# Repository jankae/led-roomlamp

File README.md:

# led-roomlamp
The led-roomlamp consists of up to six LED spots connected to a central baseplate.

Each spot features a 10W LED on a heatsink with its own (AVR controller) boost-converter (led-driver):

The spot needs a 12V supply and can be controlled via I2C. All the spots are connected to the central led-control board on the baseplate:

The led-control board essentially is just an ATmega328 with a switching controller, a microphone (one of the available MAX9814 breakout-boards) and (optionally) an ESP-01.

The controller continuously samples the microphone, performs an FFT and identifies whistle tones. By whistling different frequencies, the brightness of the lamp can be controlled.

Alternatively, the lamp can be controlled via UART (38400 Baud) which is connected to the ESP. Using the [ESP-link](https://github.com/jeelabs/esp-link) firmware, commands can be send via WiFi. Send 'help' to retrieve a list of available commands.

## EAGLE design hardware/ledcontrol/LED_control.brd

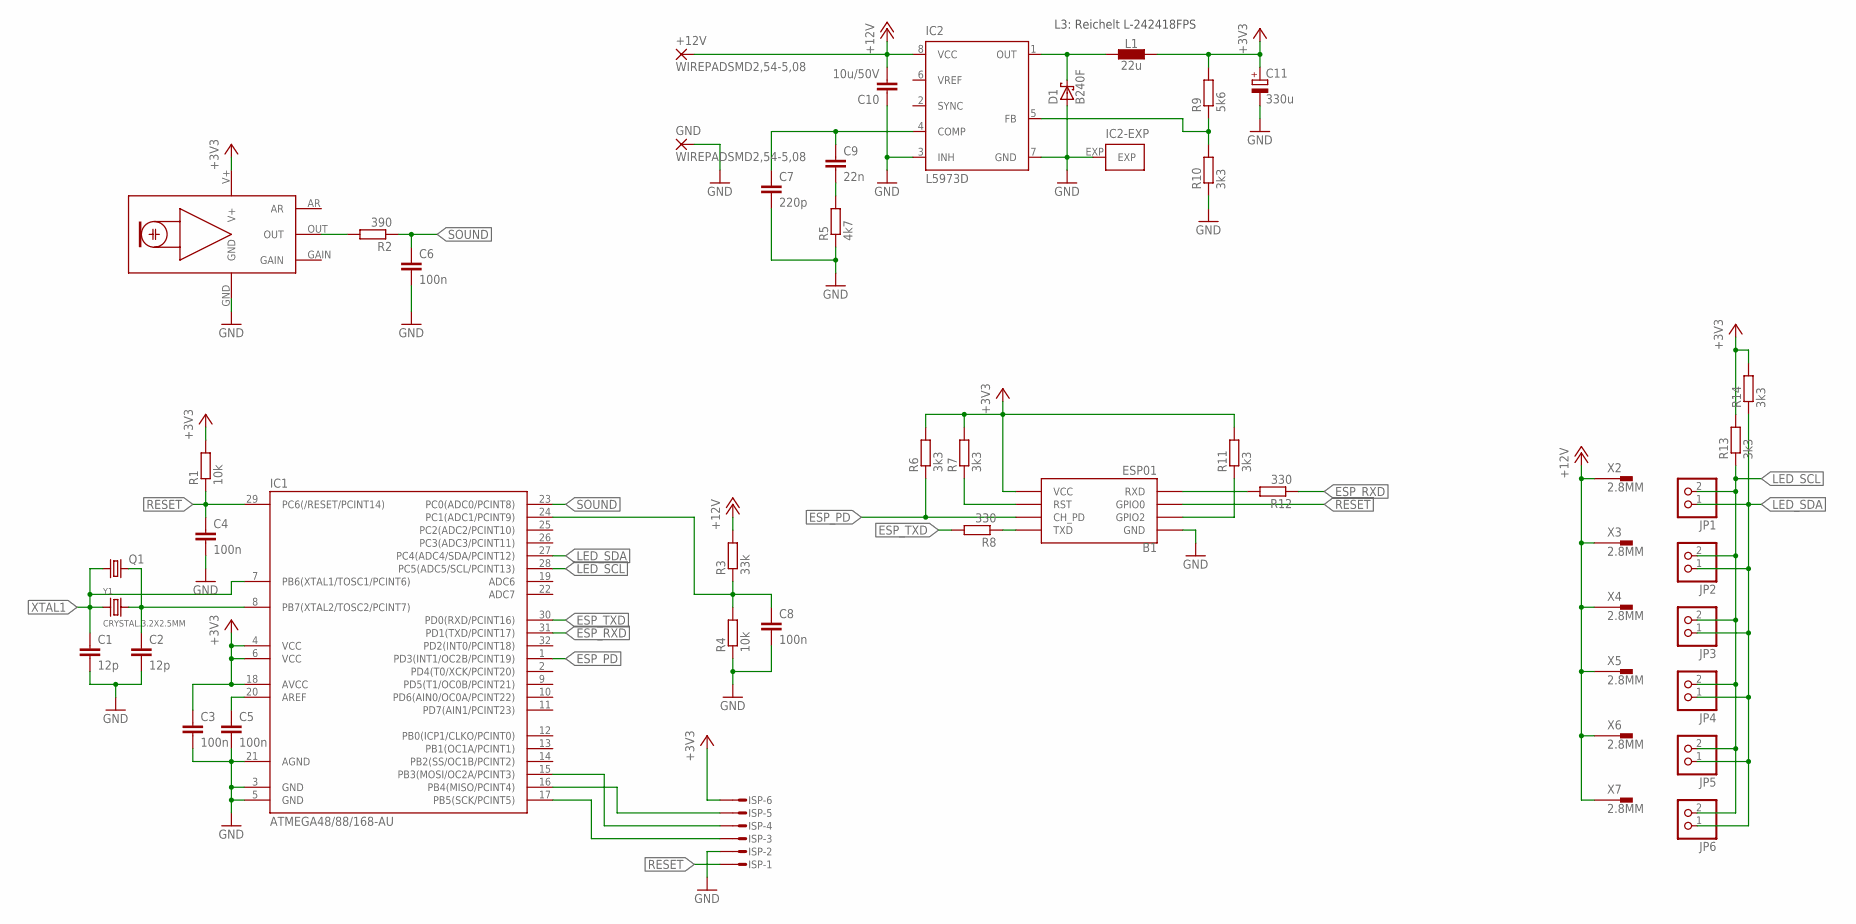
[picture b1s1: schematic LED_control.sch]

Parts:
+12V: WIREPADSMD2,54-5,08; SMD2,54-5,08
B1: ESP01
C1, C2: 12p; C0603K
C3, C5, C6: 100n; C0603K
C4, C8: 100n; C0603
C7: 220p; C0603
C9: 22n; C0603
C10: 10u/50V; C1206
C11: 330u; 153CLV-0605
D1: B240F; SMB
GND: WIREPADSMD2,54-5,08; SMD2,54-5,08
IC1: ATMEGA48/88/168-AU; TQFP32-08
IC2: L5973D; HSOP8
ISP: MICROMATCH-6SMF; MMT-F-SMD-6
JP1, JP2, JP3, JP4, JP5, JP6: PINHD-1X2/90; 1X02/90
L1: 22u; L_NR60XX
PCB1: MAX9814_AGC_MIC
Q1: CRYSTALHC49S; HC49/S
R1, R4: 10k; R0603
R2: 390; R0603
R3: 33k; R0603
R5: 4k7; R0603
R6, R7, R10, R11, R13, R14: 3k3; R0603
R8, R12: 330; R0603
R9: 5k6; R0603
X2, X3, X4, X5, X6, X7: 2.8MM; 2.8_90
Y1: CRYSTAL.3.2X2.5MM; 3.2X2.5MM

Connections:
+3V3: B1.VCC, C3.1, C11.+, IC1.4 (VCC), IC1.6 (VCC), IC1.18 (AVCC), ISP.6, L1.2, PCB1.V+, R1.2, R6.2, R7.2, R9.2, R11.2, R13.2, R14.2
+12V: +12V.1, C10.2, IC2.8 (VCC), R3.2, X2.1A, X2.1B, X3.1A, X3.1B, X4.1A, X4.1B, X5.1A, X5.1B, X6.1A, X6.1B, X7.1A, X7.1B
ESP_GPIO2: B1.GPIO2, R11.1
ESP_PD: B1.CH_PD, IC1.1 (PD3(INT1/OC2B/PCINT19)), R6.1
ESP_RST: B1.RST, R7.1
ESP_RXD: IC1.31 (PD1(TXD/PCINT17)), R12.1
ESP_TXD: IC1.30 (PD0(RXD/PCINT16)), R8.2
GND: B1.GND, C1.2, C2.2, C3.2, C4.2, C5.2, C6.2, C7.2, C8.2, C10.1, C11.-, D1.A, GND.1, IC1.3 (GND), IC1.5 (GND), IC1.21 (AGND), IC2.3 (INH), IC2.7 (GND), IC2.EXP, ISP.2, PCB1.GND, R4.1, R5.1, R10.1
LED_SCL: IC1.28 (PC5(ADC5/SCL/PCINT13)), JP1.2, JP2.2, JP3.2, JP4.2, JP5.2, JP6.2, R13.1
LED_SDA: IC1.27 (PC4(ADC4/SDA/PCINT12)), JP1.1, JP2.1, JP3.1, JP4.1, JP5.1, JP6.1, R14.1
MISO: IC1.16 (PB4(MISO/PCINT4)), ISP.5
MOSI: IC1.15 (PB3(MOSI/OC2A/PCINT3)), ISP.4
unnamed: B1.RX (RXD), R12.2
unnamed: B1.TX (TXD), R8.1
unnamed: C5.1, IC1.20 (AREF)
unnamed: PCB1.OUT, R2.2
unnamed: C8.1, IC1.24 (PC1(ADC1/PCINT9)), R3.1, R4.2
unnamed: C7.1, C9.1, IC2.4 (COMP)
unnamed: C9.2, R5.2
unnamed: D1.C, IC2.1 (OUT), L1.1
unnamed: IC2.5 (FB), R9.1, R10.2
RESET: B1.GPIO0, C4.1, IC1.29 (PC6(/RESET/PCINT14)), ISP.1, R1.1
SCK: IC1.17 (PB5(SCK/PCINT5)), ISP.3
SOUND: C6.1, IC1.23 (PC0(ADC0/PCINT8)), R2.1
XTAL1: C1.1, IC1.7 (PB6(XTAL1/TOSC1/PCINT6)), Q1.1, Y1.1
XTAL2: C2.1, IC1.8 (PB7(XTAL2/TOSC2/PCINT7)), Q1.2, Y1.3 (2)

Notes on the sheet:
L3: Reichelt L-242418FPS

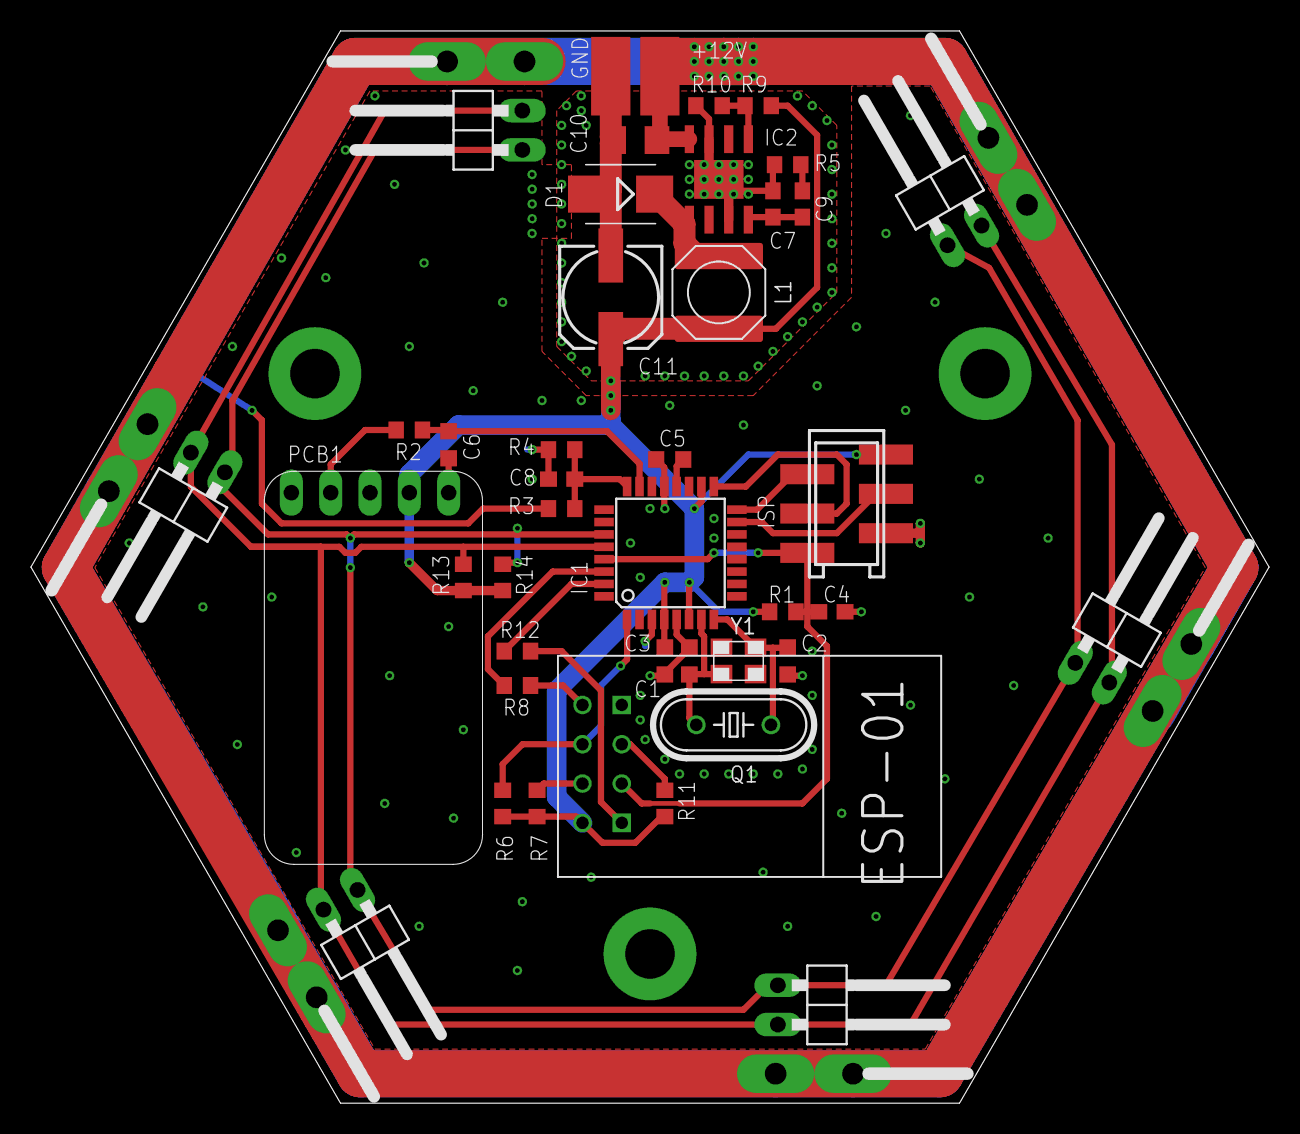
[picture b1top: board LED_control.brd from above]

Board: 2 copper layers, 80.0 x 69.3 mm, 48 parts (0 on the bottom side), 26 nets.

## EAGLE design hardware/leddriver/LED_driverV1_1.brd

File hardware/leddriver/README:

As usual, the first revision (V1) of the board includes some mistakes.
These are the necessary fixes (see fixesV1.JPG):

1. Do not populate R2.
2. Do not populate R14.
3. Do not populate Q3. Instead short its base and collector and add a resistor of approx. 10k between the emitter and collector.
4. Add a 100nF capacitor from IC1 pin 13 to ground.
5. Add a 100nF capacitor on top of R9.
6. Add a 100nF capacitor on top of R12.
7. Add a 1k resistor from R15 to ground.

These are fixed in V1.1. But since V1 is working well, V1.1 will probably never be build, is therefore untested and might contain further errors.

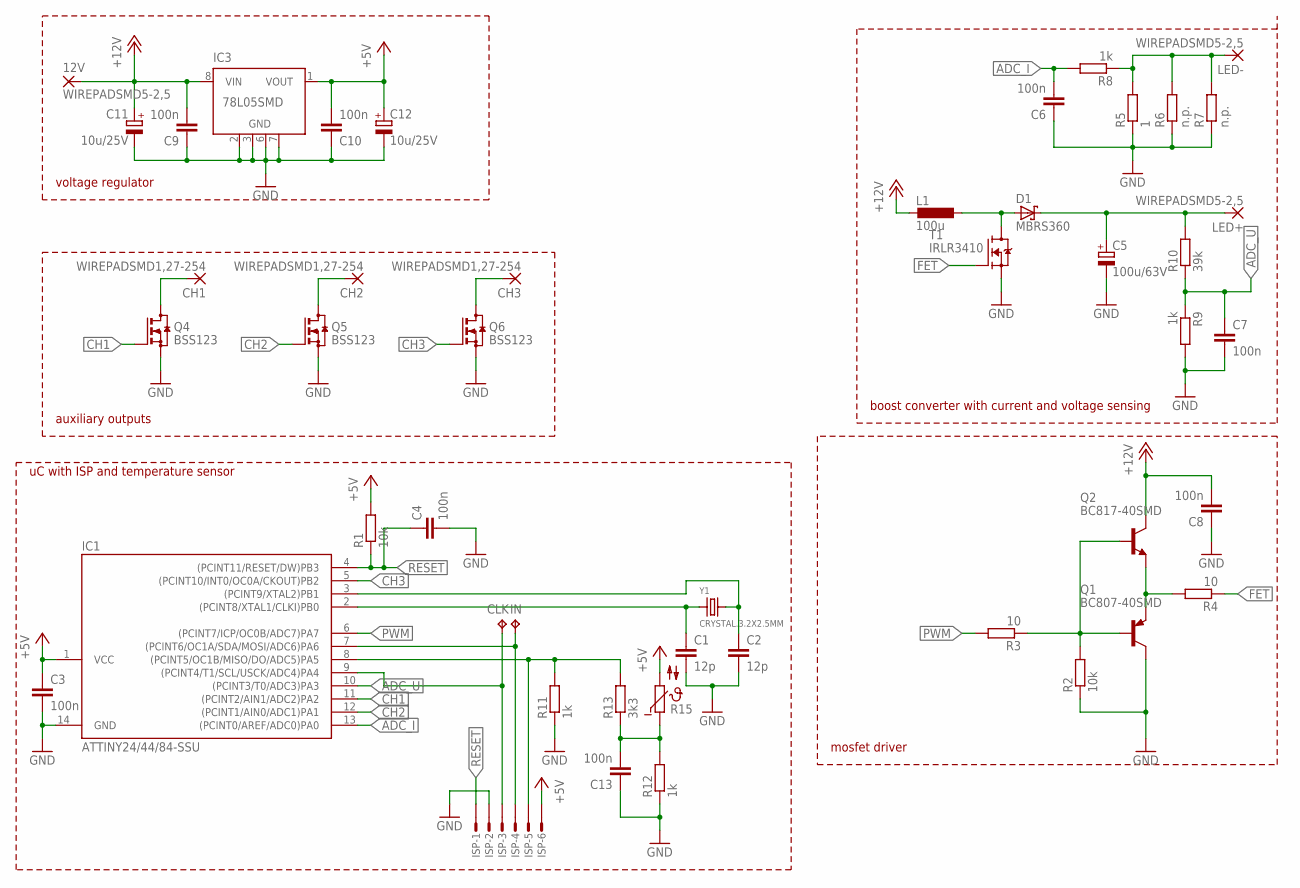
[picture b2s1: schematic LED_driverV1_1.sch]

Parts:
12V: WIREPADSMD5-2,5; 5-2,5
C1, C2: 12p; C0603K
C3, C4, C6, C7, C8, C9, C10, C13: 100n; C0603K
C5: 100u/63V; 153CLV-1010
C11, C12: 10u/25V; 153CLV-0405
CH1, CH2, CH3: WIREPADSMD1,27-254; SMD1,27-2,54
CLK: TPTP15R; TP15R
D1: MBRS360; SMC
IC1: ATTINY24/44/84-SSU; SOIC14
IC3: 78L05SMD; SO08
IN: TPTP15R; TP15R
ISP: MICROMATCH-6SMF; MMT-F-SMD-6
L1: 100u; PISM
LED+: WIREPADSMD5-2,5; 5-2,5
LED-: WIREPADSMD5-2,5; 5-2,5
Q1: BC807-40SMD; SOT23-BEC
Q2: BC817-40SMD; SOT23-BEC
Q4, Q5, Q6: BSS123; SOT23
R1, R2: 10k; R0603
R3, R4: 10; R0603
R5: 1; R1206
R6, R7: n.p.; R1206
R8, R9, R11, R12: 1k; R0603
R10: 39k; R0603
R13: 3k3; R0603
R15: NTC640; P640
T1: IRLR3410; TO252
Y1: CRYSTAL.3.2X2.5MM; 3.2X2.5MM

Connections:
+5V: C3.1, C10.2, C12.+, IC1.1 (VCC), IC3.1 (VOUT), ISP.6, R1.2, R15.2
+12V: 12V.1, C8.2, C9.2, C11.+, IC3.8 (VIN), L1.2, Q2.C
ADC_I: C6.2, IC1.13 ((PCINT0/AREF/ADC0)PA0), R8.2
ADC_U: C7.1, IC1.10 ((PCINT3/T0/ADC3)PA3), R9.1, R10.1
CH1: IC1.11 ((PCINT2/AIN1/ADC2)PA2), Q4.1 (G)
CH1_OUT: CH1.1, Q4.3 (D)
CH2: IC1.12 ((PCINT1/AIN0/ADC1)PA1), Q5.1 (G)
CH2_OUT: CH2.1, Q5.3 (D)
CH3: IC1.5 ((PCINT10/INT0/OC0A/CKOUT)PB2), Q6.1 (G)
CH3_OUT: CH3.1, Q6.3 (D)
FET: R4.1, T1.1 (G)
GND: C1.2, C2.2, C3.2, C4.2, C5.-, C6.1, C7.2, C8.1, C9.1, C10.1, C11.-, C12.-, C13.1, IC1.14 (GND), IC3.2 (GND), IC3.3 (GND), IC3.6 (GND), IC3.7 (GND), ISP.2, Q1.C, Q4.2 (S), Q5.2 (S), Q6.2 (S), R2.1, R5.1, R6.1, R7.1, R9.2, R11.1, R12.1, T1.2 (S)
LED+: C5.+, D1.C, LED+.1, R10.2
LED-: LED-.1, R5.2, R6.2, R7.2, R8.1
MISO: IC1.8 ((PCINT5/OC1B/MISO/DO/ADC5)PA5), ISP.5, R11.2, R13.2
MOSI: IC1.7 ((PCINT6/OC1A/SDA/MOSI/ADC6)PA6), IN.TP, ISP.4
unnamed: D1.A, L1.1, T1.3 (D)
PP_IN: Q1.B, Q2.B, R2.2, R3.1
PP_OUT: Q1.E, Q2.E, R4.2
PWM: IC1.6 ((PCINT7/ICP/OC0B/ADC7)PA7), R3.2
RESET: C4.1, IC1.4 ((PCINT11/RESET/DW)PB3), ISP.1, R1.1
SCK: CLK.TP, IC1.9 ((PCINT4/T1/SCL/USCK/ADC4)PA4), ISP.3
TEMP: C13.2, R12.2, R13.1, R15.1
XTAL1: C1.1, IC1.2 ((PCINT8/XTAL1/CLKI)PB0), Y1.1
XTAL2: C2.1, IC1.3 ((PCINT9/XTAL2)PB1), Y1.3 (2)

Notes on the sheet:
uC with ISP and temperature sensor
auxiliary outputs
voltage regulator
boost converter with current and voltage sensing
mosfet driver

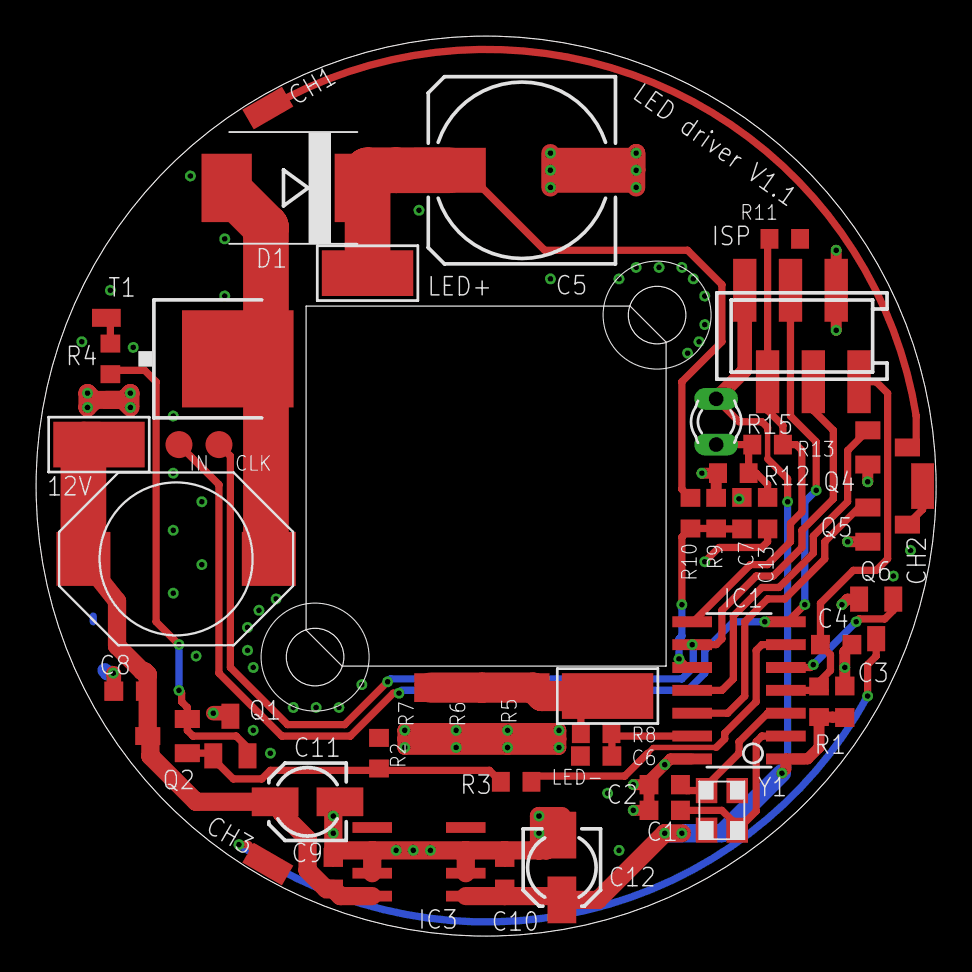
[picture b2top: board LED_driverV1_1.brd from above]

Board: 2 copper layers, 50.0 x 50.0 mm, 47 parts (0 on the bottom side), 25 nets.

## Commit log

2016-12-20 initial LED driver schmematic+layout
2016-12-20 initial software + gitignore for eclipse files
2016-12-20 missing gitignore
2016-12-21 callback in ADC interrupt
2016-12-21 serial protocol implemented, idle mode activated
2016-12-23 Python script for automatic duty-cycle/frequency calculation
2016-12-25 added make assember to makefile to view assembly
2016-12-25 Duty cycle lookup table
2017-01-02 added datasheets
2017-01-02 remove duplicate board files
2017-01-02 boost enable/disable + comments
2017-01-02 Comments and doxygen documentation
2017-01-03 temperature limit implemented
2017-01-03 serial protocol changed (not so specific anymore)
2017-01-04 some fixes + toggle macro added
2017-01-04 fixed registers and naked ISR removed
    OCR0x registers are double buffered -> not necessary anymore
2017-01-04 lots of changes
    - ADC averaging
    - ADC callback replaced by flag
    - Temperature scale adapted to 1V1 reference
2017-01-05 Software UART for debugging
2017-01-05 PWM pin changed to non-inverting, current control refined
2017-01-05 some bugfixes in serial protocol
2017-01-05 Support for current changing via SPI
2017-01-06 Serial protocol changed from SPI to I2C
2017-01-06 stop flag polling and deep sleep mode
2017-01-06 fill USI registers on boost_update
2017-01-06 don't clear stop flag
2017-01-06 boost struct values changed from raw ADC to meaningful units
    - current now in mA
    - voltage now in mV
    - temperature in °C
    - temperature calculation via lookup-table and interpolation
    - python script for generating temperatur lookup-table
2017-01-06 PWM lookup extended again + bugfixes in main
2017-01-07 [ledcontrol] initial setup, basic UART shell
2017-01-07 gitignore fixed
2017-01-07 i2c scan command added + some bugfixes
2017-01-08 inlined i2c_stop
2017-01-08 i2c read/write command
2017-01-08 basic LED control functions
2017-01-08 dummy read on check read address
2017-01-08 uart send value function
2017-01-08 ledstats command
2017-01-08 send unsigned value via uart
2017-01-08 ledset command
2017-01-08 [leddriver] USI control struct with readable names instead of registers
2017-01-08 [ledcontrol/command] bugfix: renamed option
2017-01-08 [leddriver] hysteresis for temperature limit
2017-01-08 [leddriver] temperature averaging, PWM lookup size reduced
2017-01-09 Hardware fixes + probably fixed PCB layout
2017-01-09 [leddriver] i2c fix (works so far)
2017-01-09 First picture of leddriver PCB
2017-01-09 [leddriver] Soft PWM added
2017-01-10 [leddriver] soft PWM bugfixes
2017-01-10 [ledcontrol] soft PWM protocol support
2017-01-24 Uart automations
    - Baud rate calculation using util/setbaud
    - Support for ATmega8/ATmega1284p
2017-01-24 shell echo command
2017-01-24 Switched back to ATmega1284p
2017-01-24 I2C bitrate checks
2017-01-24 Timing module added
2017-01-24 Uart defines simplified
2017-01-24 I2C timeouts
2017-01-24 Search LED spots and only do I2C operations on these addresses
2017-01-24 reset USI when switching to idle
2017-01-24 Set I2C address in makefile
2017-01-24 [bugfix] shell echo
2017-01-24 print time command
2017-01-24 [bugfix] timing ATmega8
2017-01-24 reset command
2017-01-24 Some pictures of the assembled LED spot
2017-02-09 ADC and FFT functions
2017-02-09 Minor corrections + memory saving stuff (running out of FLASH in mega8)
2017-03-17 improvements in whistle detection
2017-04-04 minor bug fixes
2017-04-20 gitignore adjustment
2017-04-20 boost control loop adjusted
2017-04-20 ledcontrol PCB files
2017-04-20 led control adjusted to mega328
2017-04-20 more images
2017-04-20 ...last picture
2017-04-20 dependency ignore
2017-07-22 Peak detection improved (at expense of some delay)
